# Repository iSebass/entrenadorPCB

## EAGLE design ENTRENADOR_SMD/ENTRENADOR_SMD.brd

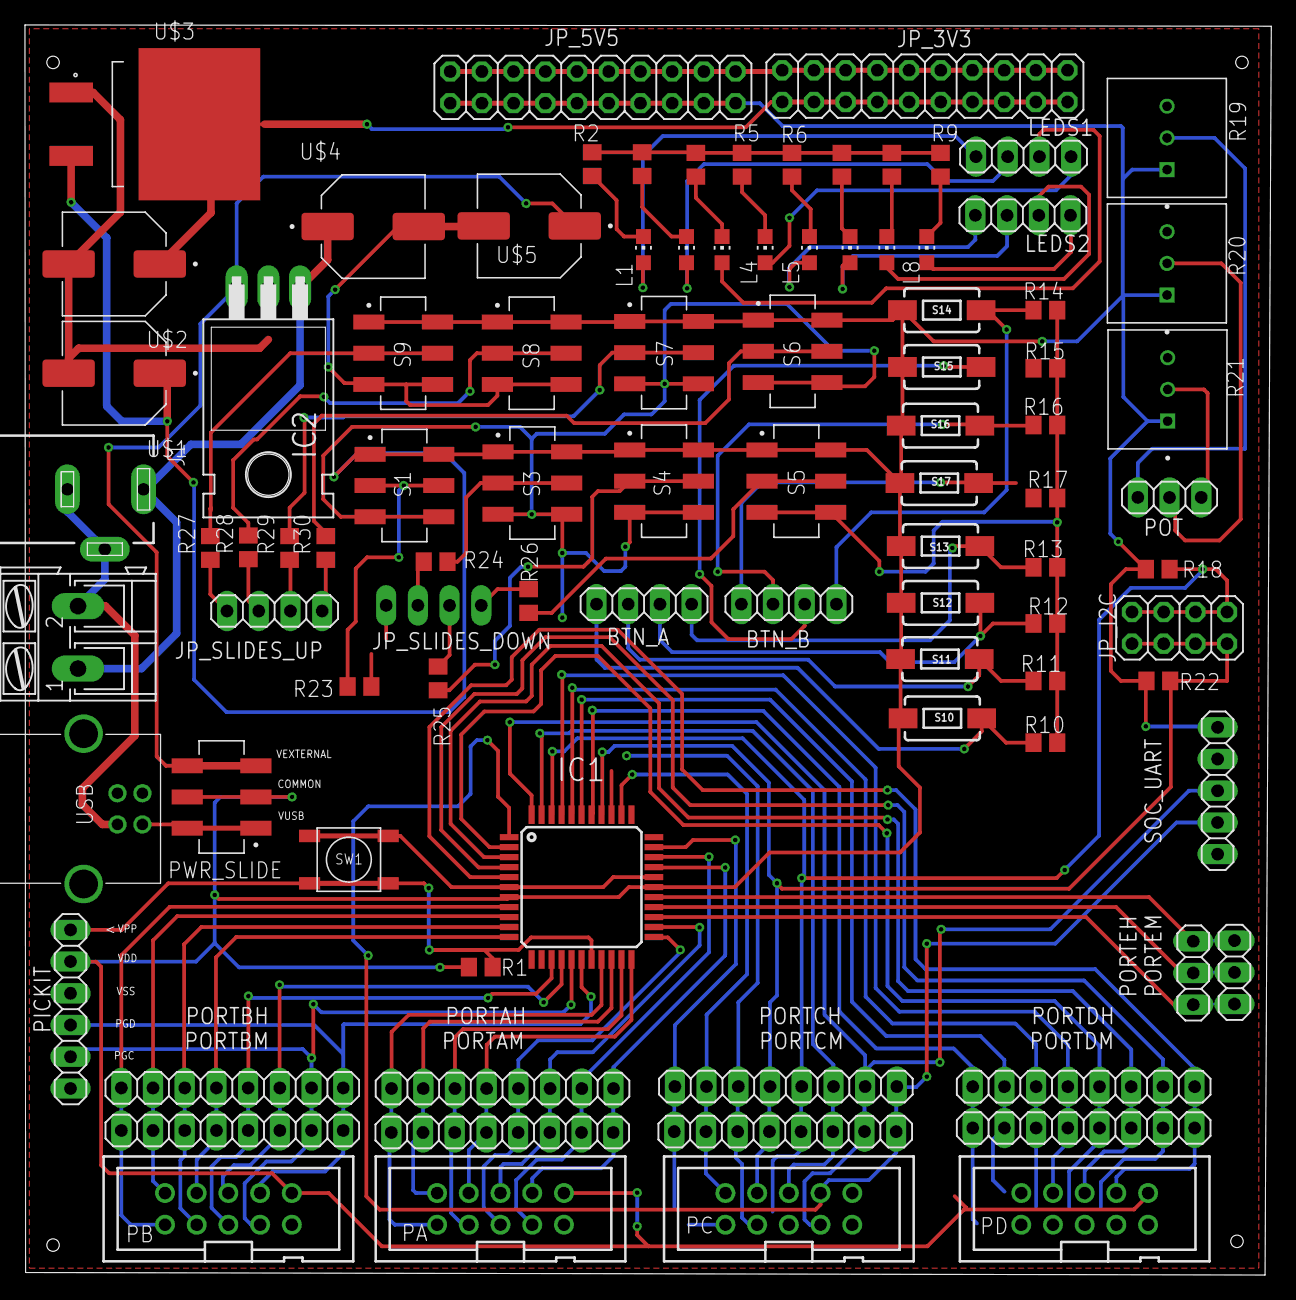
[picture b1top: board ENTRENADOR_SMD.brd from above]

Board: 2 copper layers, 99.8 x 100.2 mm, 92 parts (1 on the bottom side), 85 nets.

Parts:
BTN_A: 1X04
BTN_B: 1X04
IC1: PIC16F1939PT; TQFP44
IC2: 7824T; TO220H
J1: DCJ0202
JP_3V3, JP_5V5: 2X10
JP_I2C: 2X04
JP_SLIDES_DOWN: 1X04
JP_SLIDES_UP: 1X04
L1, L4, L5, L8: CHIP-LED0805
LED2, LED3, LED6, LED7: CHIP-LED0805
LEDS1, LEDS2: 1X04
PA: 2510-; PAK100/2500-10
PB: 2510-; PAK100/2500-10
PC: 2510-; PAK100/2500-10
PD: 2510-; PAK100/2500-10
PICKIT: 1X06
PORTAH: 1X08
PORTAM: 1X08
PORTBH: 1X08
PORTBM: 1X08
PORTCH: 1X08
PORTCM: 1X08
PORTDH: 1X08
PORTDM: 1X08
PORTEH: 1X03
PORTEM: 1X03
POT: 1X03
PWR_SLIDE: SLDS2; SW_JS202011SCQN
R1, R23, R24, R25, R26, R27, R28, R29, R30: 4K7; R0805
R2, R3, R4, R5, R6, R7, R8, R9: 330R; R0805
R10, R11, R12, R13, R14, R15, R16, R17: 10K; R0805
R18, R22: R0805
R19, R20, R21: COM-09806; TRIM_COM-09806
S1, S3, S4, S5, S6, S7, S8, S9: SLDS2; SW_JS202011SCQN
S10, S11, S12, S13, S14, S15, S16, S17: BTN1; TACTILE_SWITCH_SMD_6.0X3.5MM
SOC_UART: 1X05
SW1: TL3342F160QG/TR; SW_TL3342F160QG/TR
U$1, U$2, U$4, U$5: CAPA
U$3: VREG3V3
USB: USB_B; 85-32004-10X
X1: AK300/2

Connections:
3V3: JP_3V3.1, JP_3V3.3, JP_3V3.5, JP_3V3.7, JP_3V3.9, JP_3V3.11, JP_3V3.13, JP_3V3.15, JP_3V3.17, JP_3V3.19, U$2.P, U$3.4
GND: IC1.6, IC1.29, IC2.2, J1.2, J1.3, JP_3V3.2, JP_3V3.4, JP_3V3.6, JP_3V3.8, JP_3V3.10, JP_3V3.12, JP_3V3.14, JP_3V3.16, JP_3V3.18, JP_3V3.20, JP_5V5.2, JP_5V5.4, JP_5V5.6, JP_5V5.8, JP_5V5.10, JP_5V5.12, JP_5V5.14, JP_5V5.16, JP_5V5.18, JP_5V5.20, PA.9, PB.9, PC.9, PD.9, PICKIT.3, R2.1, R3.1, R4.1, R5.1, R6.1, R7.1, R8.1, R9.1, R10.1, R11.1, R12.1, R13.1, R14.1, R15.1, R16.1, R17.1, R19.3, R20.3, R21.3, S1.3, S1.6, S3.3, S3.6, S4.3, S4.6, S5.3, S5.6, S6.3, S6.6, S7.3, S7.6, S8.3, S8.6, S9.3, S9.6, SOC_UART.4, SW1.1, SW1.2, U$1.N, U$2.N, U$3.1, U$4.N, U$5.N, USB.4, X1.2
MCLR: IC1.18, PICKIT.1, R1.1, SW1.3, SW1.4
unnamed: R23.2, S1.2, S1.5
unnamed: R24.2, S3.2, S3.5
unnamed: R25.2, S4.2, S4.5
unnamed: R26.2, S5.2, S5.5
unnamed: R30.2, S6.2, S6.5
unnamed: R29.2, S7.2, S7.5
unnamed: R28.2, S8.2, S8.5
unnamed: R27.2, S9.2, S9.5
unnamed: L1.C, R2.2
unnamed: LED2.C, R3.2
unnamed: LED3.C, R4.2
unnamed: L4.C, R5.2
unnamed: L5.C, R6.2
unnamed: LED6.C, R7.2
unnamed: LED7.C, R8.2
unnamed: L8.C, R9.2
unnamed: L1.A, LEDS1.1
unnamed: LED2.A, LEDS1.2
unnamed: LED3.A, LEDS1.3
unnamed: L4.A, LEDS1.4
unnamed: L5.A, LEDS2.1
unnamed: LED6.A, LEDS2.2
unnamed: LED7.A, LEDS2.3
unnamed: L8.A, LEDS2.4
unnamed: BTN_A.1, R10.2, S10.1
unnamed: BTN_A.2, R11.2, S11.1
unnamed: BTN_A.3, R12.2, S12.1
unnamed: BTN_A.4, R13.2, S13.1
unnamed: BTN_B.4, R14.2, S14.1
unnamed: BTN_B.3, R15.2, S15.1
unnamed: BTN_B.2, R16.2, S16.1
unnamed: BTN_B.1, R17.2, S17.1
unnamed: POT.3, R21.2
unnamed: POT.2, R20.2
unnamed: POT.1, R19.2
unnamed: IC2.1, J1.1, U$4.P, X1.1
unnamed: JP_SLIDES_UP.1, R27.1
unnamed: JP_SLIDES_UP.2, R28.1
unnamed: JP_SLIDES_UP.3, R29.1
unnamed: JP_SLIDES_DOWN.1, R26.1
unnamed: JP_SLIDES_DOWN.2, R25.1
unnamed: JP_SLIDES_DOWN.3, R24.1
unnamed: JP_SLIDES_DOWN.4, R23.1
unnamed: JP_SLIDES_UP.4, R30.1
RA0: IC1.19, PA.1, PORTAH.1, PORTAM.1
RA1: IC1.20, PA.2, PORTAH.2, PORTAM.2
RA2: IC1.21, PA.3, PORTAH.3, PORTAM.3
RA3: IC1.22, PA.4, PORTAH.4, PORTAM.4
RA4: IC1.23, PA.5, PORTAH.5, PORTAM.5
RA5: IC1.24, PA.6, PORTAH.6, PORTAM.6
RA6: IC1.31, PA.7, PORTAH.7, PORTAM.7
RA7: IC1.30, PA.8, PORTAH.8, PORTAM.8
RB0: IC1.8, PB.1, PORTBH.1, PORTBM.1
RB1: IC1.9, PB.2, PORTBH.2, PORTBM.2
RB2: IC1.10, PB.3, PORTBH.3, PORTBM.3
RB3: IC1.11, PB.4, PORTBH.4, PORTBM.4
RB4: IC1.14, PB.5, PORTBH.5, PORTBM.5
RB5: IC1.15, PB.6, PORTBH.6, PORTBM.6
RB6: IC1.16, PB.7, PICKIT.5, PORTBH.7, PORTBM.7
RB7: IC1.17, PB.8, PICKIT.4, PORTBH.8, PORTBM.8
RC0: IC1.32, PC.1, PORTCH.1, PORTCM.1
RC1: IC1.35, PC.2, PORTCH.2, PORTCM.2
RC2: IC1.36, PC.3, PORTCH.3, PORTCM.3
RC3: IC1.37, JP_I2C.2, JP_I2C.4, JP_I2C.6, JP_I2C.8, PC.4, PORTCH.4, PORTCM.4, R22.1
RC4: IC1.42, JP_I2C.1, JP_I2C.3, JP_I2C.5, JP_I2C.7, PC.5, PORTCH.5, PORTCM.5, R18.1
RC5: IC1.43, PC.6, PORTCH.6, PORTCM.6
RC6: IC1.44, PC.7, PORTCH.7, PORTCM.7, SOC_UART.3
RC7: IC1.1, PC.8, PORTCH.8, PORTCM.8, SOC_UART.2
RD0: IC1.38, PD.1, PORTDH.1, PORTDM.1
RD1: IC1.39, PD.2, PORTDH.2, PORTDM.2
RD2: IC1.40, PD.3, PORTDH.3, PORTDM.3
RD3: IC1.41, PD.4, PORTDH.4, PORTDM.4
RD4: IC1.2, PD.5, PORTDH.5, PORTDM.5
RD5: IC1.3, PD.6, PORTDH.6, PORTDM.6
RD6: IC1.4, PD.7, PORTDH.7, PORTDM.7
RD7: IC1.5, PD.8, PORTDH.8, PORTDM.8
RE0: IC1.25, PORTEH.1, PORTEM.1
RE1: IC1.26, PORTEH.2, PORTEM.2
RE2: IC1.27, PORTEH.3, PORTEM.3
VCC: IC1.7, IC1.28, JP_5V5.1, JP_5V5.3, JP_5V5.5, JP_5V5.7, JP_5V5.9, JP_5V5.11, JP_5V5.13, JP_5V5.15, JP_5V5.17, JP_5V5.19, PA.10, PB.10, PC.10, PD.10, PICKIT.2, PWR_SLIDE.2, PWR_SLIDE.5, R1.2, R18.2, R19.1, R20.1, R21.1, R22.2, S1.1, S1.4, S3.1, S3.4, S4.1, S4.4, S5.1, S5.4, S6.1, S6.4, S7.1, S7.4, S8.1, S8.4, S9.1, S9.4, S10.2, S11.2, S12.2, S13.2, S14.2, S15.2, S16.2, S17.2, SOC_UART.5, U$1.P, U$3.3
VEXT: IC2.3, PWR_SLIDE.3, PWR_SLIDE.6, U$5.P
VUSB: PWR_SLIDE.1, PWR_SLIDE.4, USB.1

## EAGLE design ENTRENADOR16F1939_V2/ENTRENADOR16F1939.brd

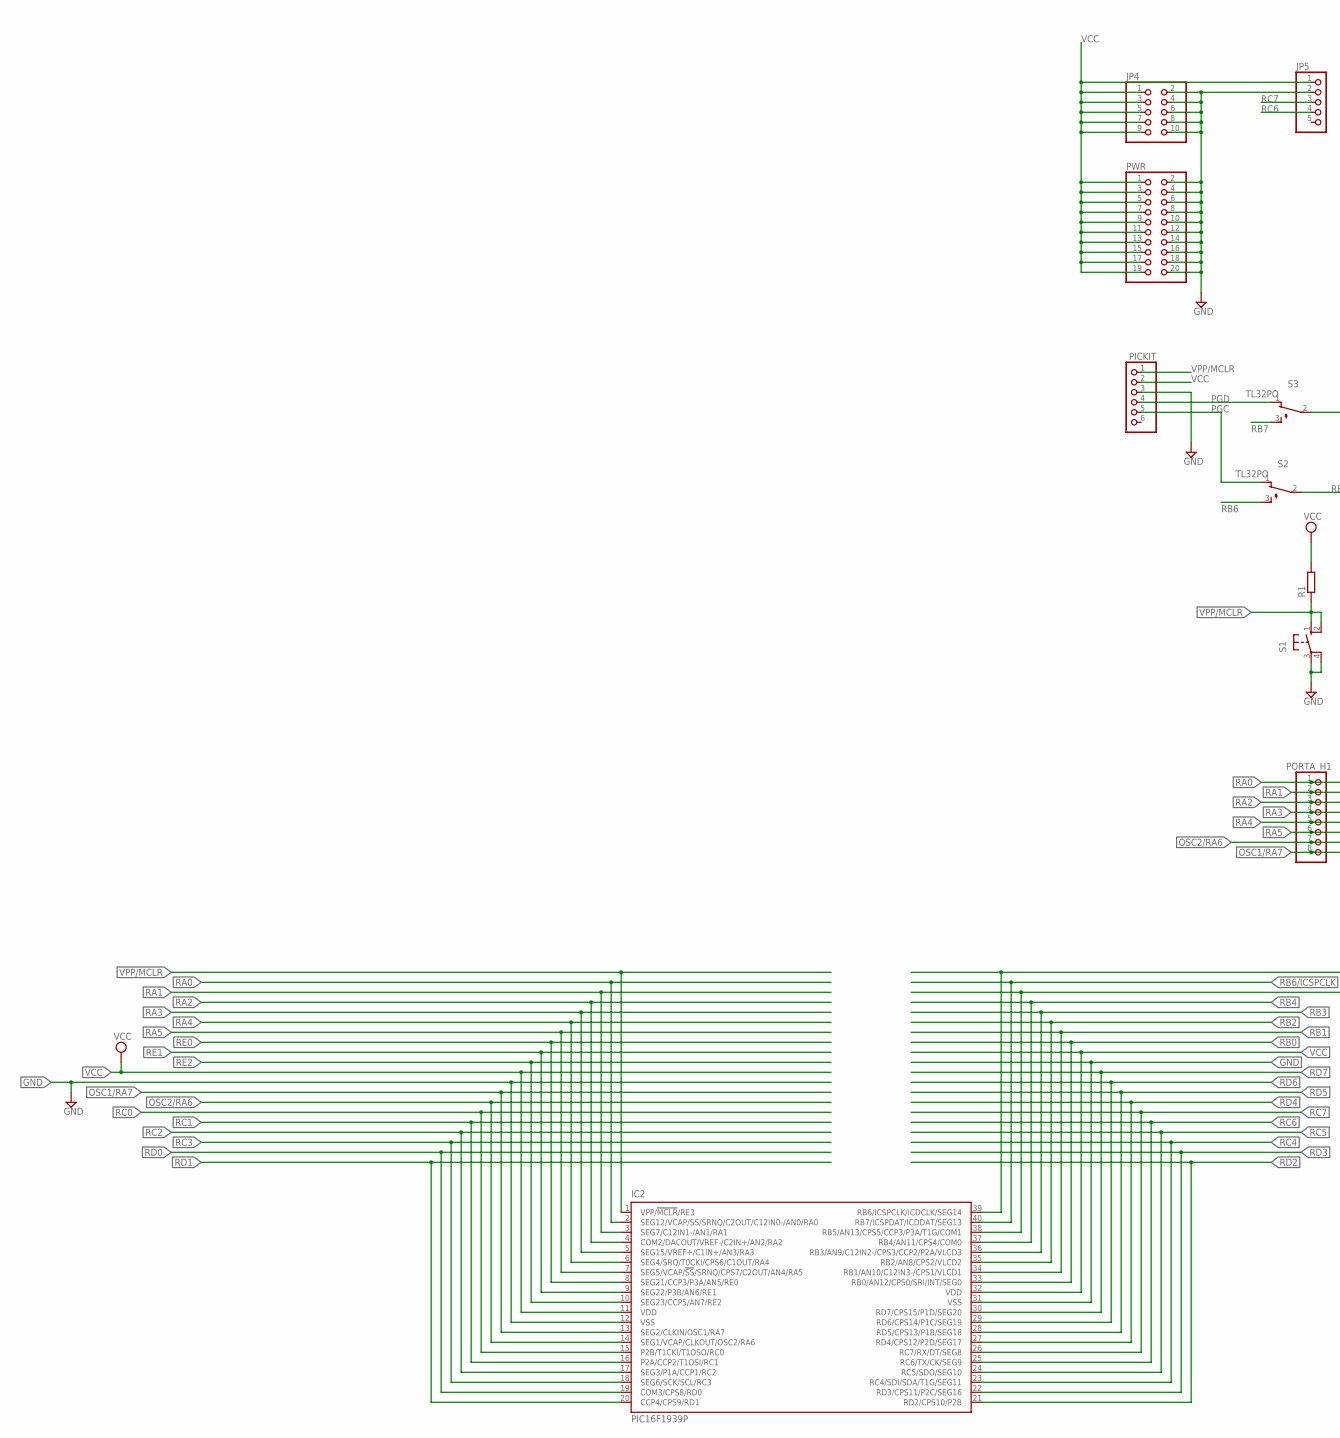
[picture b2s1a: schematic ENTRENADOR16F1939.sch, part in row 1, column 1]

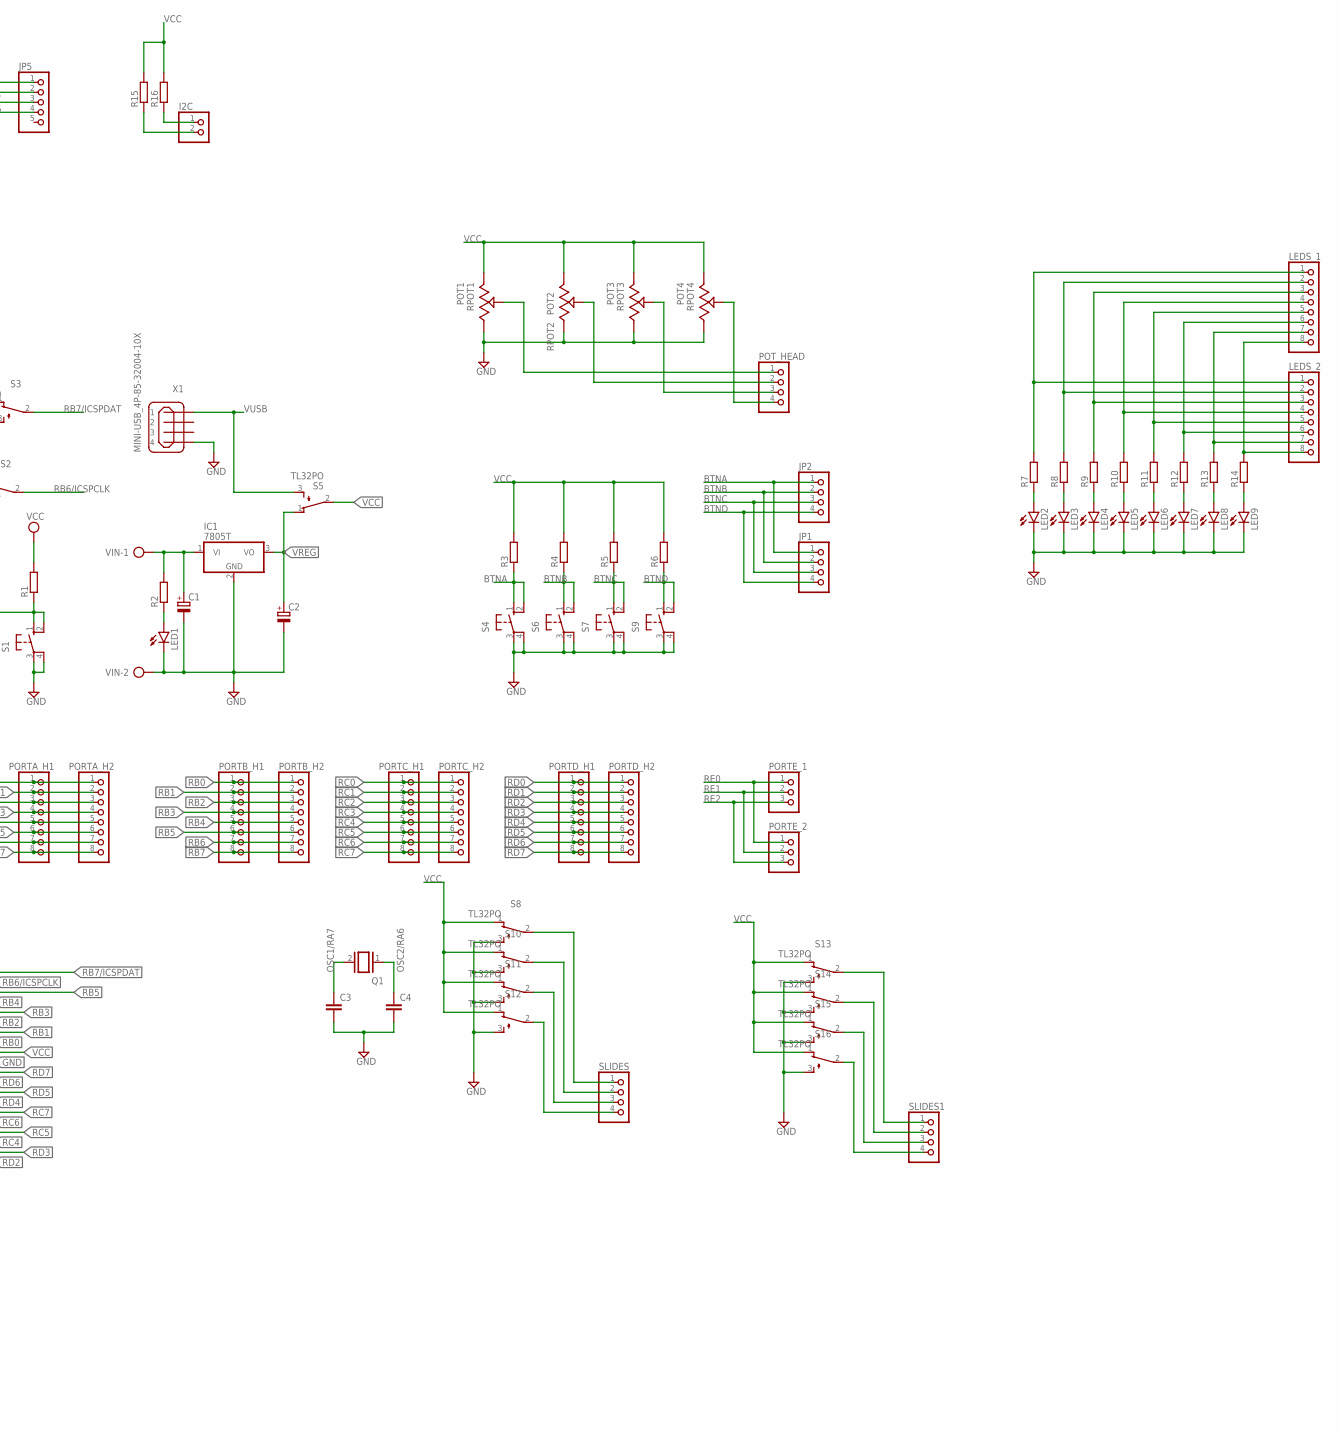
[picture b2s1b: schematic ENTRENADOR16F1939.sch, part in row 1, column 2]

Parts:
C1, C2: CPOL-EUE2.5-6; E2,5-6
C3, C4: C-EU025-024X044; C025-024X044
I2C: PINHD-1X2; 1X02
IC1: 7805T; TO220H
IC2: PIC16F1939P; DIL40
JP1, JP2: PINHD-1X4; 1X04
JP4: PINHD-2X5; 2X05
JP5: PINHD-1X5; 1X05
LED1, LED2, LED3, LED4, LED5, LED6, LED7, LED8, LED9: LED3MM
LEDS_1, LEDS_2: PINHD-1X8; 1X08
PICKIT: PINHD-1X6; 1X06
PORTA_H1, PORTA_H2: PINHD-1X8; 1X08
PORTB_H1, PORTB_H2: PINHD-1X8; 1X08
PORTC_H1, PORTC_H2: PINHD-1X8; 1X08
PORTD_H1, PORTD_H2: PINHD-1X8; 1X08
PORTE_1, PORTE_2: PINHD-1X3; 1X03
POT1: RPOT1; TRIM_3386P-1-101TLF
POT2: RPOT2; TRIM_3386P-1-101TLF
POT3: RPOT3; TRIM_3386P-1-101TLF
POT4: RPOT4; TRIM_3386P-1-101TLF
POT_HEAD: PINHD-1X4; 1X04
PWR: PINHD-2X10; 2X10
Q1: XTAL/S; QS
R1, R2, R3, R4, R5, R6, R7, R8, R9, R10, R11, R12, R13, R14, R15, R16: R-EU_0204/7; 0204/7
S1, S4, S6, S7, S9: 10-XX; B3F-10XX
S2, S3, S5, S8, S10, S11, S12, S13, S14, S15, S16: TL32PO; TL3XPO
SLIDES, SLIDES1: PINHD-1X4; 1X04
VIN: AK300/2
X1: MINI-USB_4P-85-32004-10X; 85-32004-10X

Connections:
BTNA: JP1.1, JP2.1, R3.1, S4.1 (S), S4.2 (S1)
BTNB: JP1.2, JP2.2, R4.1, S6.1 (S), S6.2 (S1)
BTNC: JP1.3, JP2.3, R5.1, S7.1 (S), S7.2 (S1)
BTND: JP1.4, JP2.4, R6.1, S9.1 (S), S9.2 (S1)
GND: C1.-, C2.-, C3.2, C4.2, IC1.2 (GND), IC2.12 (VSS), IC2.31 (VSS), JP4.2, JP4.4, JP4.6, JP4.8, JP4.10, JP5.2, LED1.K (C), LED2.K (C), LED3.K (C), LED4.K (C), LED5.K (C), LED6.K (C), LED7.K (C), LED8.K (C), LED9.K (C), PICKIT.3, POT1.3 (CW), POT2.3 (CW), POT3.3 (CW), POT4.3 (CW), PWR.2, PWR.4, PWR.6, PWR.8, PWR.10, PWR.12, PWR.14, PWR.16, PWR.18, PWR.20, S1.3, S1.4 (P1), S4.3, S4.4 (P1), S6.3, S6.4 (P1), S7.3, S7.4 (P1), S8.3 (S), S9.3, S9.4 (P1), S10.3 (S), S11.3 (S), S12.3 (S), S13.3 (S), S14.3 (S), S15.3 (S), S16.3 (S), VIN.2, X1.4
unnamed: C1.+, IC1.1 (VI), R2.2, VIN.1
unnamed: LED2.A, R7.1
unnamed: LED1.A, R2.1
unnamed: LED3.A, R8.1
unnamed: LED4.A, R9.1
unnamed: LED5.A, R10.1
unnamed: LED6.A, R11.1
unnamed: LED7.A, R12.1
unnamed: LED8.A, R13.1
unnamed: LED9.A, R14.1
unnamed: LEDS_1.8, LEDS_2.8, R14.2
unnamed: LEDS_1.7, LEDS_2.7, R13.2
unnamed: LEDS_1.6, LEDS_2.6, R12.2
unnamed: LEDS_1.5, LEDS_2.5, R11.2
unnamed: LEDS_1.4, LEDS_2.4, R10.2
unnamed: LEDS_1.3, LEDS_2.3, R9.2
unnamed: LEDS_1.2, LEDS_2.2, R8.2
unnamed: LEDS_1.1, LEDS_2.1, R7.2
unnamed: S12.2, SLIDES.4
unnamed: S8.2, SLIDES.1
unnamed: S10.2, SLIDES.2
unnamed: S11.2, SLIDES.3
unnamed: POT1.2 (WIPER), POT_HEAD.1
unnamed: POT2.2 (WIPER), POT_HEAD.2
unnamed: POT3.2 (WIPER), POT_HEAD.3
unnamed: POT4.2 (WIPER), POT_HEAD.4
unnamed: I2C.2, R15.1
unnamed: I2C.1, R16.1
unnamed: S13.2, SLIDES1.1
unnamed: S14.2, SLIDES1.2
unnamed: S15.2, SLIDES1.3
unnamed: S16.2, SLIDES1.4
OSC1/RA7: C3.1, IC2.13 (SEG2/CLKIN/OSC1/RA7), PORTA_H1.8, PORTA_H2.8, Q1.2
OSC2/RA6: C4.1, IC2.14 (SEG1/VCAP/CLKOUT/OSC2/RA6), PORTA_H1.7, PORTA_H2.7, Q1.1
PGC: PICKIT.5, S2.1 (O)
PGD: PICKIT.4, S3.1 (O)
RA0: IC2.2 (SEG12/VCAP/SS/SRNQ/C2OUT/C12IN0-/AN0/RA0), PORTA_H1.1, PORTA_H2.1
RA1: IC2.3 (SEG7/C12IN1-/AN1/RA1), PORTA_H1.2, PORTA_H2.2
RA2: IC2.4 (COM2/DACOUT/VREF-/C2IN+/AN2/RA2), PORTA_H1.3, PORTA_H2.3
RA3: IC2.5 (SEG15/VREF+/C1IN+/AN3/RA3), PORTA_H1.4, PORTA_H2.4
RA4: IC2.6 (SEG4/SRQ/T0CKI/CPS6/C1OUT/RA4), PORTA_H1.5, PORTA_H2.5
RA5: IC2.7 (SEG5/VCAP/!SS!/SRNQ/CPS7/C2OUT/AN4/RA5), PORTA_H1.6, PORTA_H2.6
RB0: IC2.33 (RB0/AN12/CPS0/SRI/INT/SEG0), PORTB_H1.1, PORTB_H2.1
RB1: IC2.34 (RB1/AN10/C12IN3-/CPS1/VLCD1), PORTB_H1.2, PORTB_H2.2
RB2: IC2.35 (RB2/AN8/CPS2/VLCD2), PORTB_H1.3, PORTB_H2.3
RB3: IC2.36 (RB3/AN9/C12IN2-/CPS3/CCP2/P2A/VLCD3), PORTB_H1.4, PORTB_H2.4
RB4: IC2.37 (RB4/AN11/CPS4/COM0), PORTB_H1.5, PORTB_H2.5
RB5: IC2.38 (RB5/AN13/CPS5/CCP3/P3A/T1G/COM1), PORTB_H1.6, PORTB_H2.6
RB6: PORTB_H1.7, PORTB_H2.7, S2.3 (S)
RB6/ICSPCLK: IC2.40 (RB7/ICSPDAT/ICDDAT/SEG13), S2.2
RB7: PORTB_H1.8, PORTB_H2.8, S3.3 (S)
RB7/ICSPDAT: IC2.39 (RB6/ICSPCLK/ICDCLK/SEG14), S3.2
RC0: IC2.15 (P2B/T1CKI/T1OSO/RC0), PORTC_H1.1, PORTC_H2.1
RC1: IC2.16 (P2A/CCP2/T1OSI/RC1), PORTC_H1.2, PORTC_H2.2
RC2: IC2.17 (SEG3/P1A/CCP1/RC2), PORTC_H1.3, PORTC_H2.3
RC3: IC2.18 (SEG6/SCK/SCL/RC3), PORTC_H1.4, PORTC_H2.4
RC4: IC2.23 (RC4/SDI/SDA/T1G/SEG11), PORTC_H1.5, PORTC_H2.5
RC5: IC2.24 (RC5/SDO/SEG10), PORTC_H1.6, PORTC_H2.6
RC6: IC2.25 (RC6/TX/CK/SEG9), JP5.4, PORTC_H1.7, PORTC_H2.7
RC7: IC2.26 (RC7/RX/DT/SEG8), JP5.3, PORTC_H1.8, PORTC_H2.8
RD0: IC2.19 (COM3/CPS8/RD0), PORTD_H1.1, PORTD_H2.1
RD1: IC2.20 (CCP4/CPS9/RD1), PORTD_H1.2, PORTD_H2.2
RD2: IC2.21 (RD2/CPS10/P2B), PORTD_H1.3, PORTD_H2.3
RD3: IC2.22 (RD3/CPS11/P2C/SEG16), PORTD_H1.4, PORTD_H2.4
RD4: IC2.27 (RD4/CPS12/P2D/SEG17), PORTD_H1.5, PORTD_H2.5
RD5: IC2.28 (RD5/CPS13/P1B/SEG18), PORTD_H1.6, PORTD_H2.6
RD6: IC2.29 (RD6/CPS14/P1C/SEG19), PORTD_H1.7, PORTD_H2.7
RD7: IC2.30 (RD7/CPS15/P1D/SEG20), PORTD_H1.8, PORTD_H2.8
RE0: IC2.8 (SEG21/CCP3/P3A/AN5/RE0), PORTE_1.1, PORTE_2.1
RE1: IC2.9 (SEG22/P3B/AN6/RE1), PORTE_1.2, PORTE_2.2
RE2: IC2.10 (SEG23/CCP5/AN7/RE2), PORTE_1.3, PORTE_2.3
VCC: IC2.11 (VDD), IC2.32 (VDD), JP4.1, JP4.3, JP4.5, JP4.7, JP4.9, JP5.1, PICKIT.2, POT1.1 (CCW), POT2.1 (CCW), POT3.1 (CCW), POT4.1 (CCW), PWR.1, PWR.3, PWR.5, PWR.7, PWR.9, PWR.11, PWR.13, PWR.15, PWR.17, PWR.19, R1.2, R3.2, R4.2, R5.2, R6.2, R15.2, R16.2, S5.2, S8.1 (O), S10.1 (O), S11.1 (O), S12.1 (O), S13.1 (O), S14.1 (O), S15.1 (O), S16.1 (O)
VPP/MCLR: IC2.1 (VPP/!MCLR!/RE3), PICKIT.1, R1.1, S1.1 (S), S1.2 (S1)
VREG: C2.+, IC1.3 (VO), S5.1 (O)
VUSB: S5.3 (S), X1.1

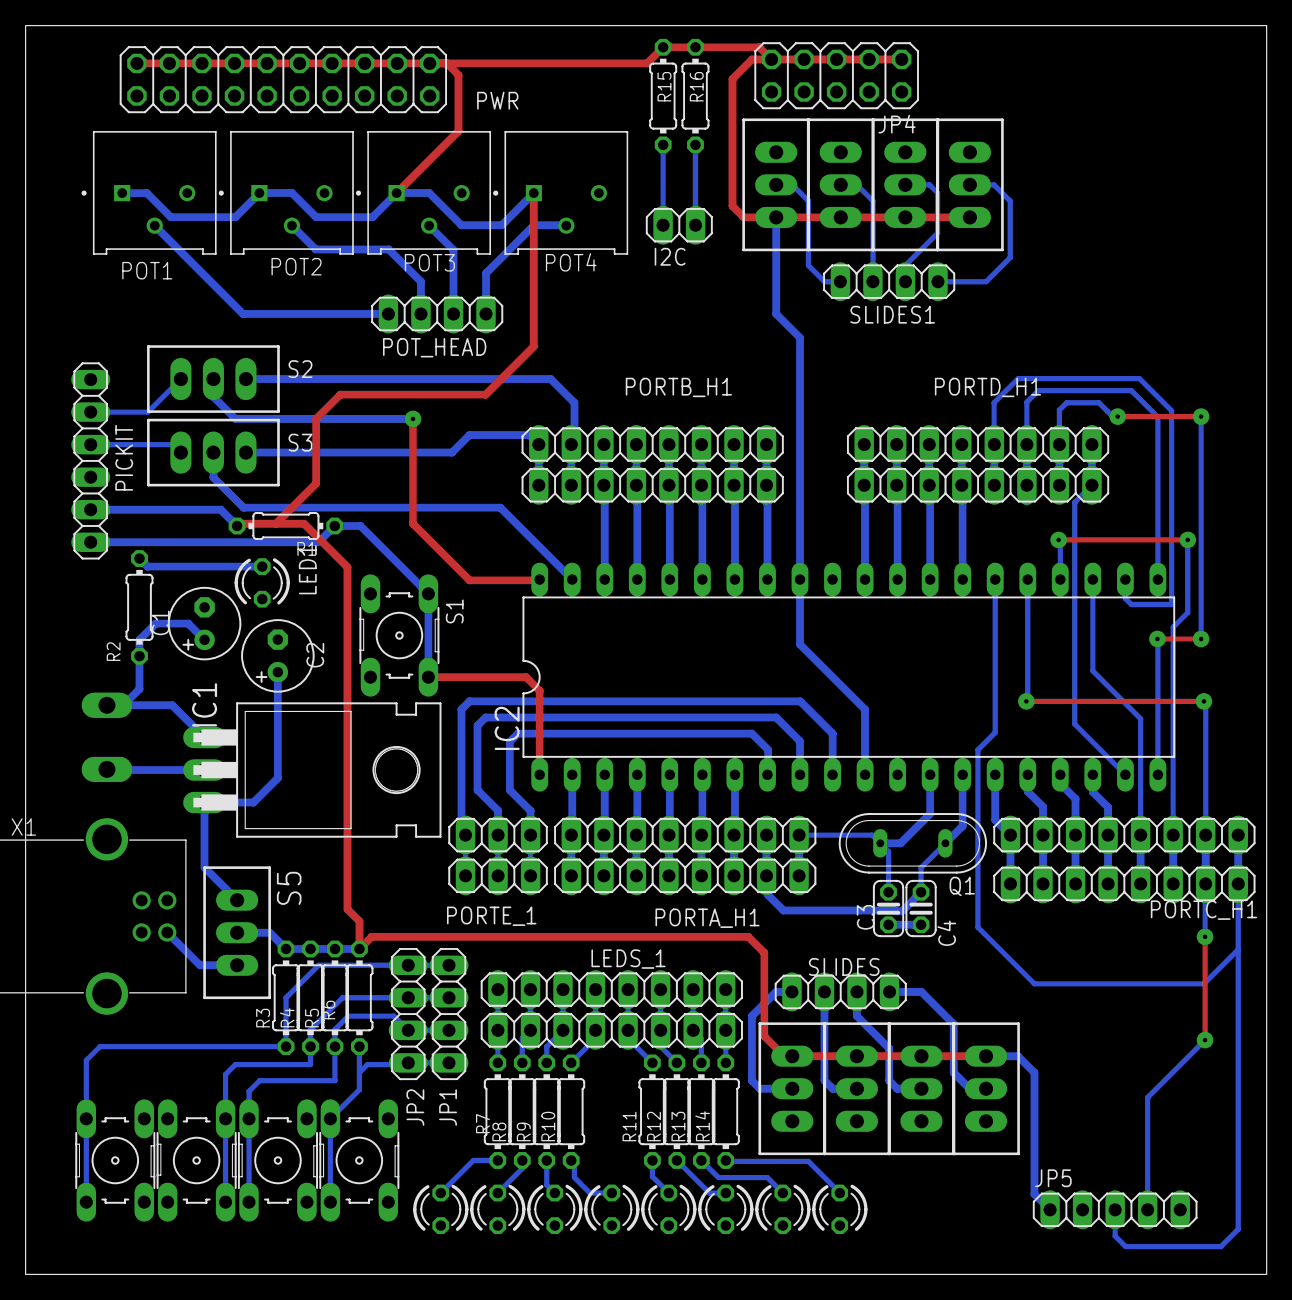
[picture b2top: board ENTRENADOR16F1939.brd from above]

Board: 2 copper layers, 96.9 x 97.5 mm, 76 parts (1 on the bottom side), 80 nets.

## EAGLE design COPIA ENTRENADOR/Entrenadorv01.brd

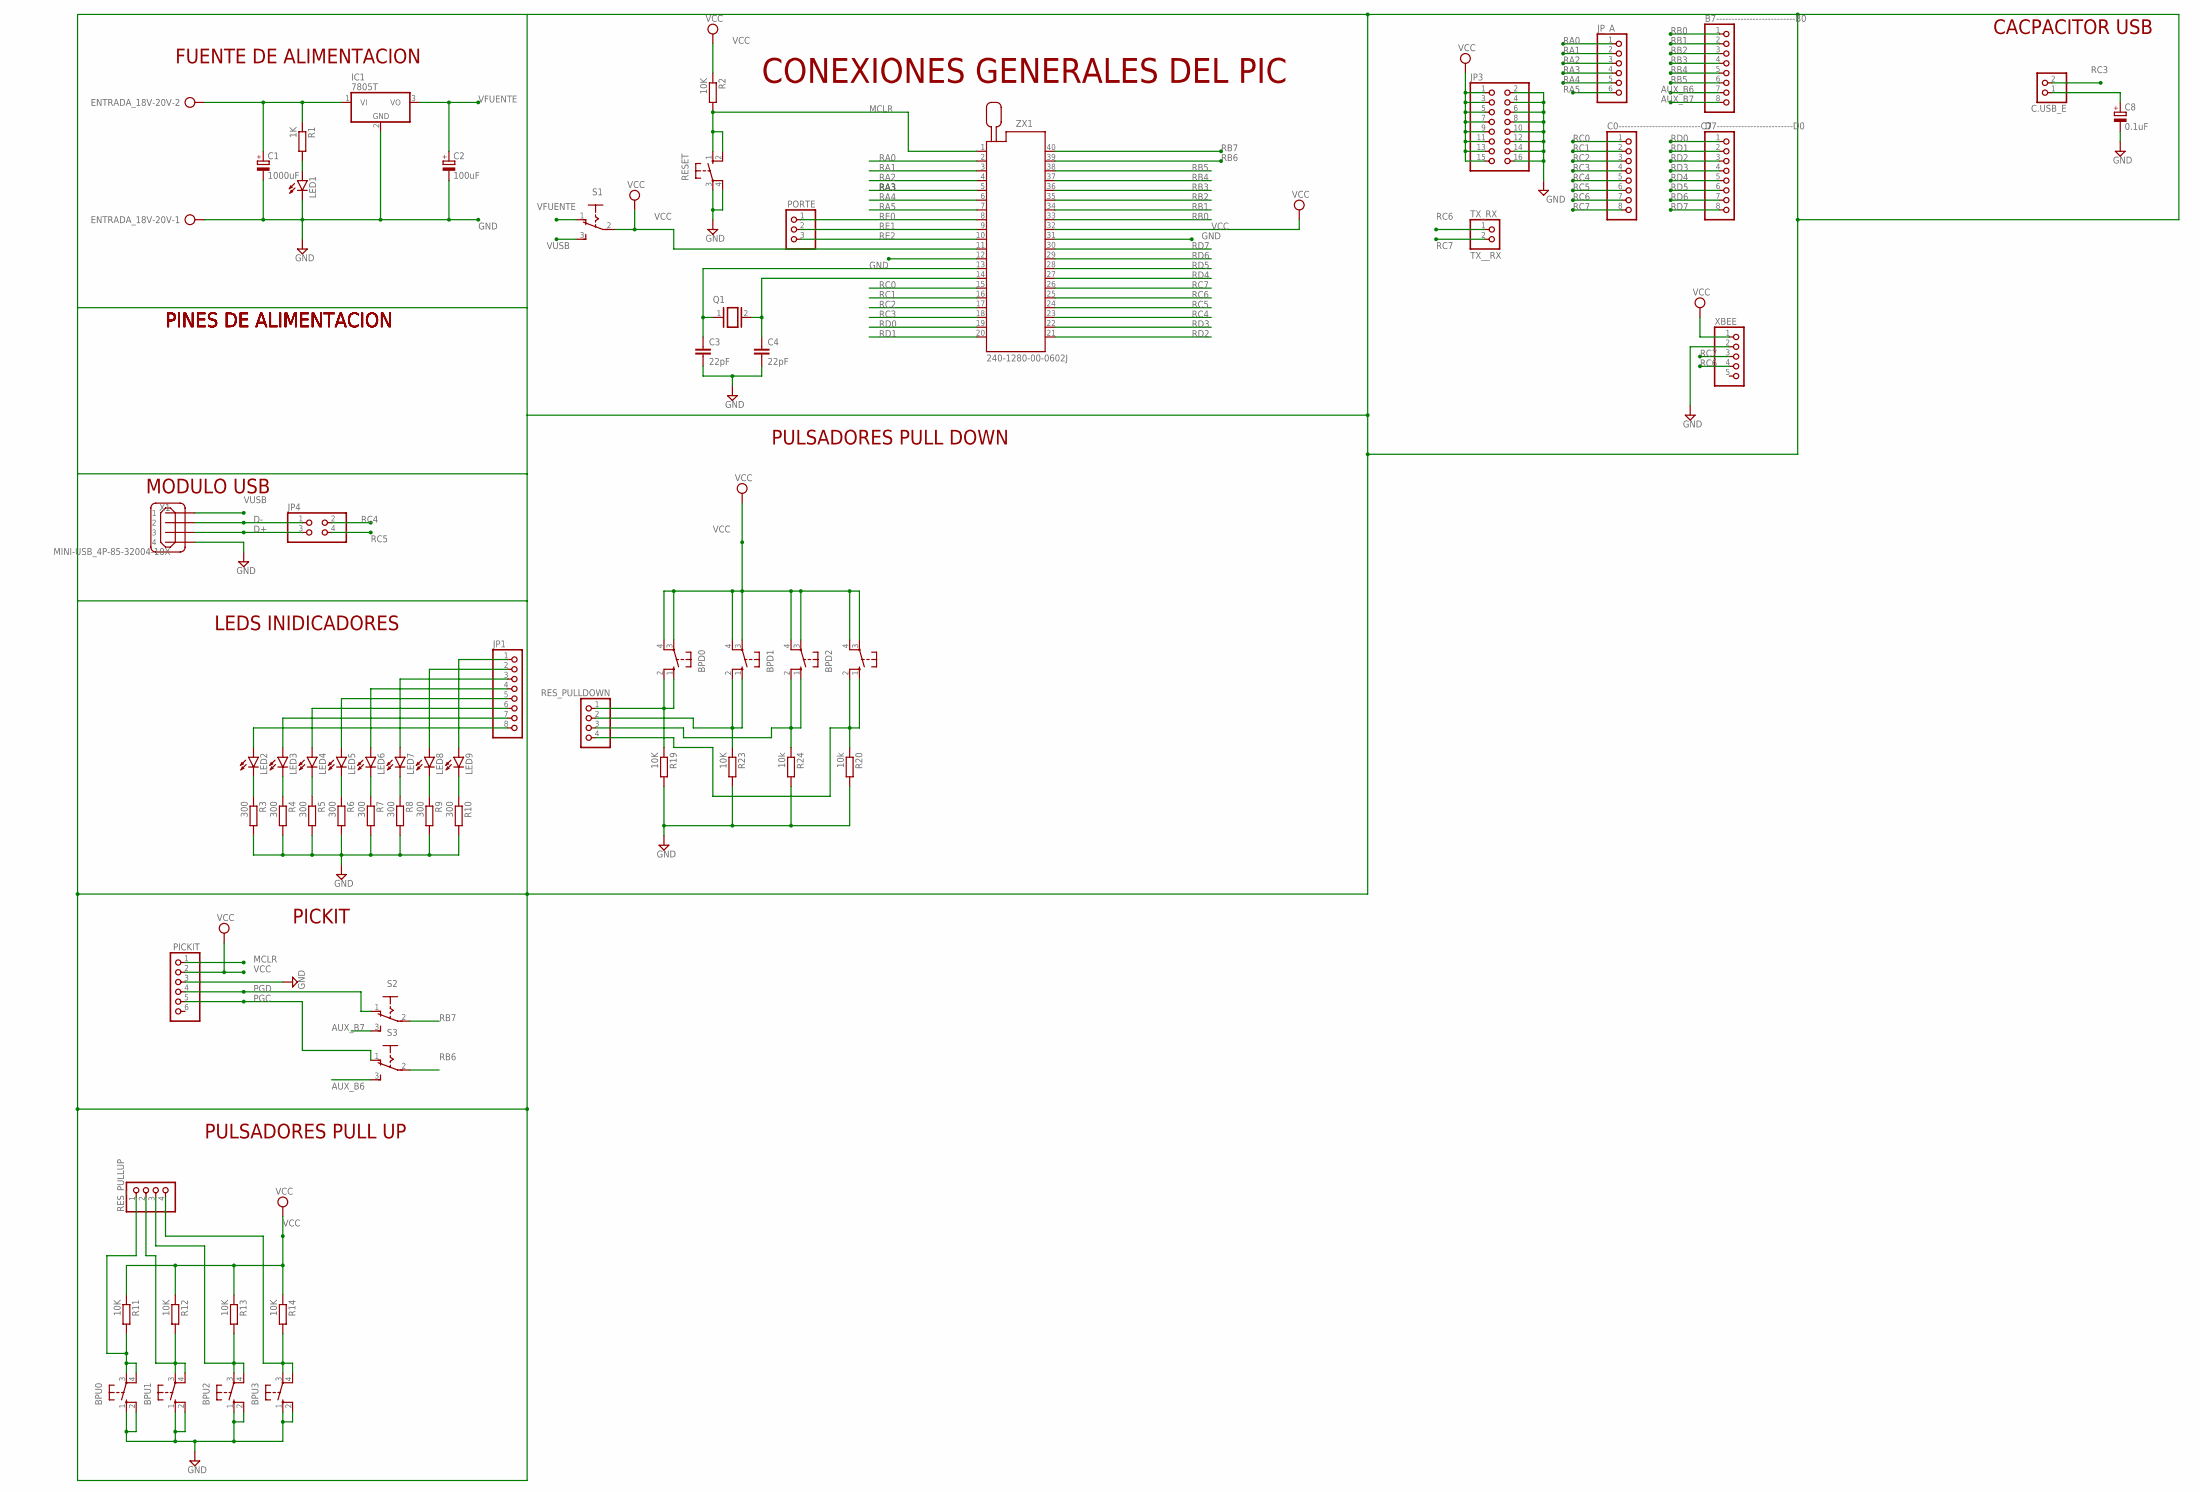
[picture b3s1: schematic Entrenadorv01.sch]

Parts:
B7--------------------------B0: PINHD-1X8; 1X08
BPD0, BPD1, BPD2, BPD3: 10-XX; B3F-10XX
BPU0, BPU1, BPU2, BPU3: 10-XX; B3F-10XX
C0---------------------------C7: PINHD-1X8; 1X08
C1: 1000uF; E5-10,5
C2: 100uF; E5-10,5
C3, C4: 22pF; C025-025X050
C8: 0.1uF; E1,8-4
C.USB_E: PINHD-1X2; 1X02
D7-------------------------D0: PINHD-1X8; 1X08
ENTRADA_18V-20V: AK300/2
IC1: 7805T; TO220H
JP1: PINHD-1X8; 1X08
JP3: PINHD-2X8; 2X08
JP4: PINHD-2X2; 2X02
JP_A: PINHD-1X6; 1X06
LED1, LED2, LED3, LED4, LED5, LED6, LED7, LED8, LED9: LED3MM
PICKIT: PINHD-1X6; 1X06
PORTE: PINHD-1X3; 1X03
Q1: XTAL/S; QS
R1: 1K; 0207/10
R2, R11, R12, R13, R14, R19, R23: 10K; 0207/10
R3, R4, R5, R6, R7, R8, R9, R10: 300; 0207/10
R20, R24: 10k; 0207/10
RESET: 10-XX; B3F-10XX
RES_PULLDOWN: PINHD-1X4; 1X04
RES_PULLUP: PINHD-1X4; 1X04
S1, S2, S3: M251
TX_RX: TX__RX; 1X02
X1: MINI-USB_4P-85-32004-10X; 85-32004-10X
XBEE: PINHD-1X5; 1X05
ZX1: 240-1280-00-0602J

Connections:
AUX_B6: B7--------------------------B0.7, S3.3 (S)
AUX_B7: B7--------------------------B0.8, S2.3 (S)
D+: JP4.3, X1.3
D-: JP4.1, X1.2
GND: BPU0.1 (S), BPU0.2 (S1), BPU1.1 (S), BPU1.2 (S1), BPU2.1 (S), BPU2.2 (S1), BPU3.1 (S), BPU3.2 (S1), C1.-, C2.-, C3.2, C4.2, C8.-, ENTRADA_18V-20V.1, IC1.2 (GND), JP3.2, JP3.4, JP3.6, JP3.8, JP3.10, JP3.12, JP3.14, JP3.16, LED1.K (C), PICKIT.3, R3.2, R4.2, R5.2, R6.2, R7.2, R8.2, R9.2, R10.2, R19.2, R20.2, R23.2, R24.2, RESET.3, RESET.4 (P1), X1.4, XBEE.2, ZX1.12, ZX1.31
MCLR: PICKIT.1, R2.2, RESET.1 (S), RESET.2 (S1), ZX1.1
unnamed: C1.+, ENTRADA_18V-20V.2, IC1.1 (VI), R1.1
unnamed: BPU0.3, BPU0.4 (P1), R11.2, RES_PULLUP.1
unnamed: LED1.A, R1.2
unnamed: BPU1.3, BPU1.4 (P1), R12.2, RES_PULLUP.2
unnamed: C3.1, Q1.1, ZX1.13
unnamed: C4.1, Q1.2, ZX1.14
unnamed: BPD0.1 (S), BPD0.2 (S1), R19.1, RES_PULLDOWN.1
unnamed: BPU2.3, BPU2.4 (P1), R13.2, RES_PULLUP.3
unnamed: BPU3.3, BPU3.4 (P1), R14.2, RES_PULLUP.4
unnamed: BPD1.1 (S), BPD1.2 (S1), R23.1, RES_PULLDOWN.2
unnamed: BPD2.1 (S), BPD2.2 (S1), R24.1, RES_PULLDOWN.3
unnamed: BPD3.1 (S), BPD3.2 (S1), R20.1, RES_PULLDOWN.4
unnamed: LED2.K (C), R3.1
unnamed: LED3.K (C), R4.1
unnamed: LED4.K (C), R5.1
unnamed: LED5.K (C), R6.1
unnamed: LED6.K (C), R7.1
unnamed: LED7.K (C), R8.1
unnamed: LED8.K (C), R9.1
unnamed: LED9.K (C), R10.1
unnamed: JP1.1, LED9.A
unnamed: JP1.2, LED8.A
unnamed: JP1.3, LED7.A
unnamed: JP1.4, LED6.A
unnamed: JP1.5, LED5.A
unnamed: JP1.6, LED4.A
unnamed: JP1.7, LED3.A
unnamed: JP1.8, LED2.A
unnamed: C8.+, C.USB_E.1
PGC: PICKIT.5, S3.1 (O)
PGD: PICKIT.4, S2.1 (O)
RA0: JP_A.1, ZX1.2
RA1: JP_A.2, ZX1.3
RA2: JP_A.3, ZX1.4
RA3: JP_A.4, ZX1.5
RA4: JP_A.5, ZX1.6
RA5: JP_A.6, ZX1.7
RB0: B7--------------------------B0.1, ZX1.33
RB1: B7--------------------------B0.2, ZX1.34
RB2: B7--------------------------B0.3, ZX1.35
RB3: B7--------------------------B0.4, ZX1.36
RB4: B7--------------------------B0.5, ZX1.37
RB5: B7--------------------------B0.6, ZX1.38
RB6: S3.2, ZX1.39
RB7: S2.2, ZX1.40
RC0: C0---------------------------C7.1, ZX1.15
RC1: C0---------------------------C7.2, ZX1.16
RC2: C0---------------------------C7.3, ZX1.17
RC3: C0---------------------------C7.4, C.USB_E.2, ZX1.18
RC4: C0---------------------------C7.5, JP4.2, ZX1.23
RC5: C0---------------------------C7.6, JP4.4, ZX1.24
RC6: C0---------------------------C7.7, TX_RX.1, XBEE.4, ZX1.25
RC7: C0---------------------------C7.8, TX_RX.2, XBEE.3, ZX1.26
RD0: D7-------------------------D0.1, ZX1.19
RD1: D7-------------------------D0.2, ZX1.20
RD2: D7-------------------------D0.3, ZX1.21
RD3: D7-------------------------D0.4, ZX1.22
RD4: D7-------------------------D0.5, ZX1.27
RD5: D7-------------------------D0.6, ZX1.28
RD6: D7-------------------------D0.7, ZX1.29
RD7: D7-------------------------D0.8, ZX1.30
RE0: PORTE.1, ZX1.8
RE1: PORTE.2, ZX1.9
RE2: PORTE.3, ZX1.10
VCC: BPD0.3, BPD0.4 (P1), BPD1.3, BPD1.4 (P1), BPD2.3, BPD2.4 (P1), BPD3.3, BPD3.4 (P1), JP3.1, JP3.3, JP3.5, JP3.7, JP3.9, JP3.11, JP3.13, JP3.15, PICKIT.2, R2.1, R11.1, R12.1, R13.1, R14.1, S1.2, XBEE.1, ZX1.11, ZX1.32
VFUENTE: C2.+, IC1.3 (VO), S1.1 (O)
VUSB: S1.3 (S), X1.1

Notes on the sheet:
FUENTE DE ALIMENTACION
CONEXIONES GENERALES DEL PIC
PINES DE ALIMENTACION
MODULO USB
LEDS INIDICADORES
PICKIT
PULSADORES PULL UP
PULSADORES PULL DOWN
CACPACITOR USB

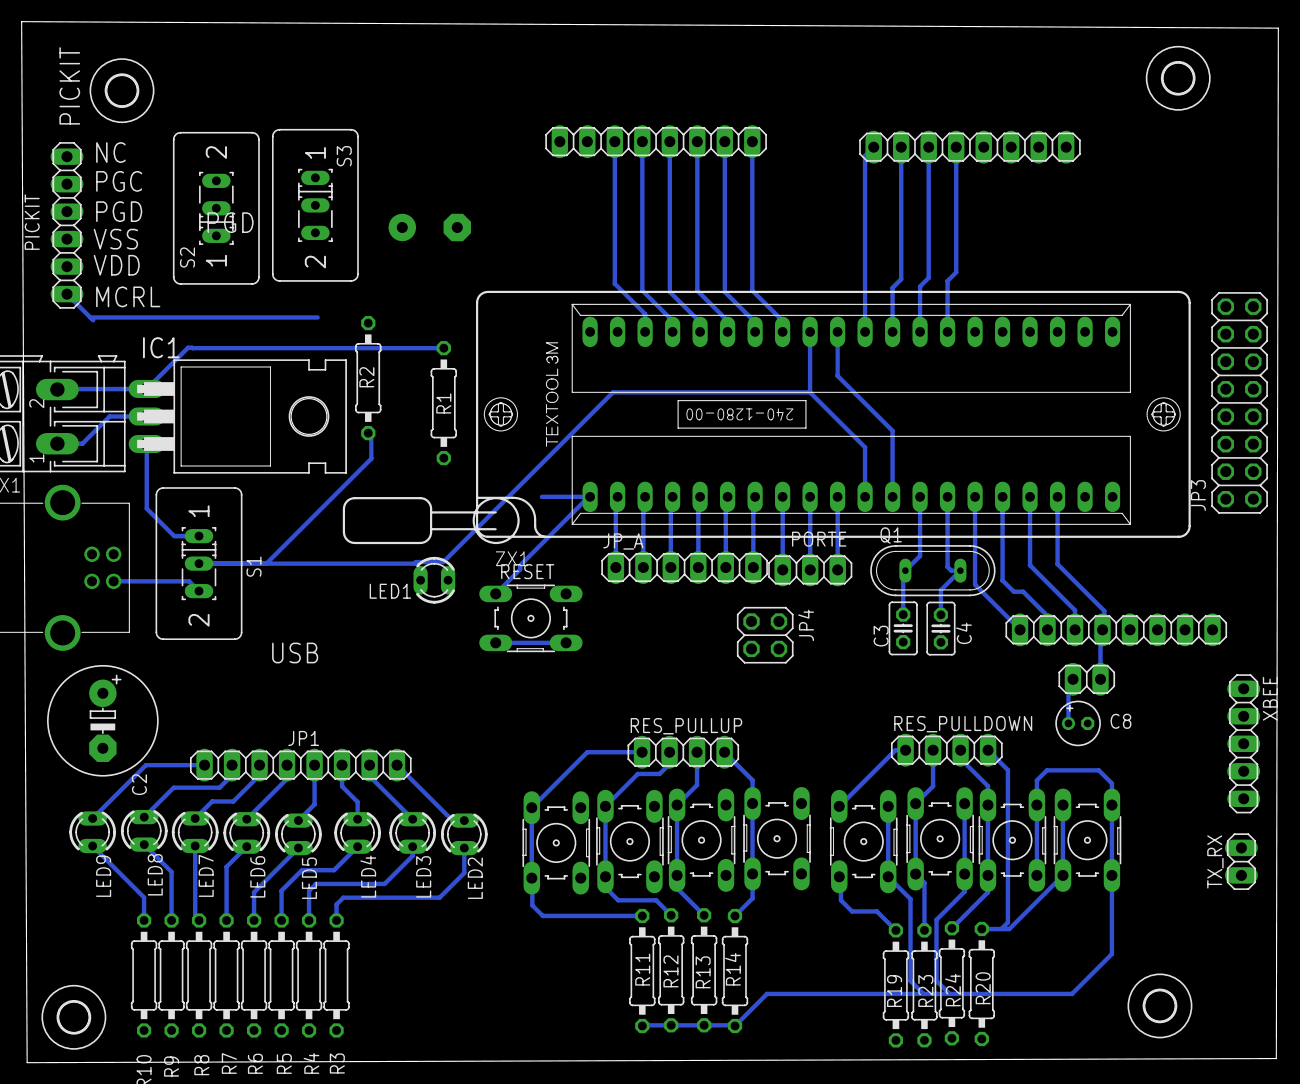
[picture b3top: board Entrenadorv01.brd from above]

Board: 2 copper layers, 116.1 x 96.2 mm, 67 parts (1 on the bottom side), 73 nets.

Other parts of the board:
U$3, U$4, U$5, U$6: 2,8

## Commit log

2023-06-07 Se agregan archivos de PCB
2023-06-22 Se agregan nuevos diseños
2023-06-23 Se actualiza y se argegan librerias
2023-06-26 se crea diseño entrenador
2023-07-07 Se agrega prototipo final
2023-08-09 Se ajusta el PCB SMD en perforacion
2023-08-09 Se agrega lista de componentes
2023-08-22 se agrega diseño PCB
